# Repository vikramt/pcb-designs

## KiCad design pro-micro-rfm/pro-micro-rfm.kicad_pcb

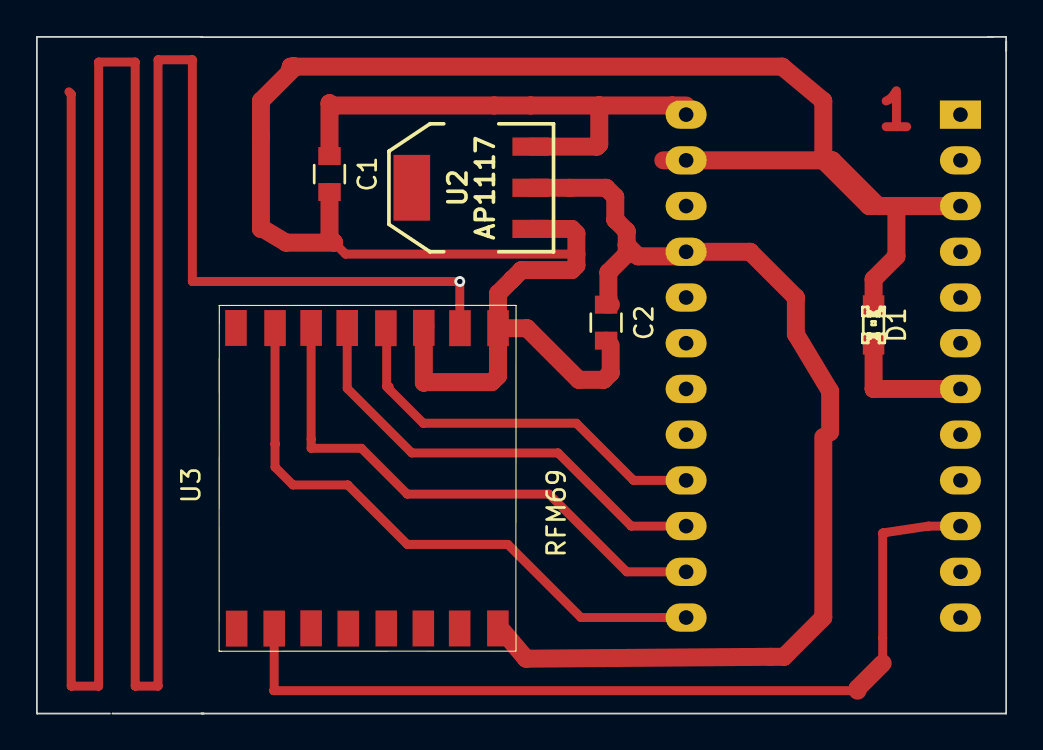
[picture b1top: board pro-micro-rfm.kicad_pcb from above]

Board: 2 copper layers, 53.8 x 37.6 mm, 6 parts (1 on the bottom side), 9 nets.

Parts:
C1, C2: C; C_0805
D1: LED; LED-0805
U1: ProMicro; ARDUINO_PRO_MINI
U2: AP1117; SOT223
U3: RFM69; RFM69HW

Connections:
GND: C1.2, C2.2, D1.1, U1.3, U1.23, U2.1, U3.9, U3.11
unnamed: C1.1, U1.24, U2.3
unnamed: C2.1, U1.21, U2.2, U3.8
unnamed: D1.2, U1.7
unnamed: U1.10, U3.2
unnamed: U1.13, U3.15
unnamed: U1.14, U3.14
unnamed: U1.15, U3.13
unnamed: U1.16, U3.12

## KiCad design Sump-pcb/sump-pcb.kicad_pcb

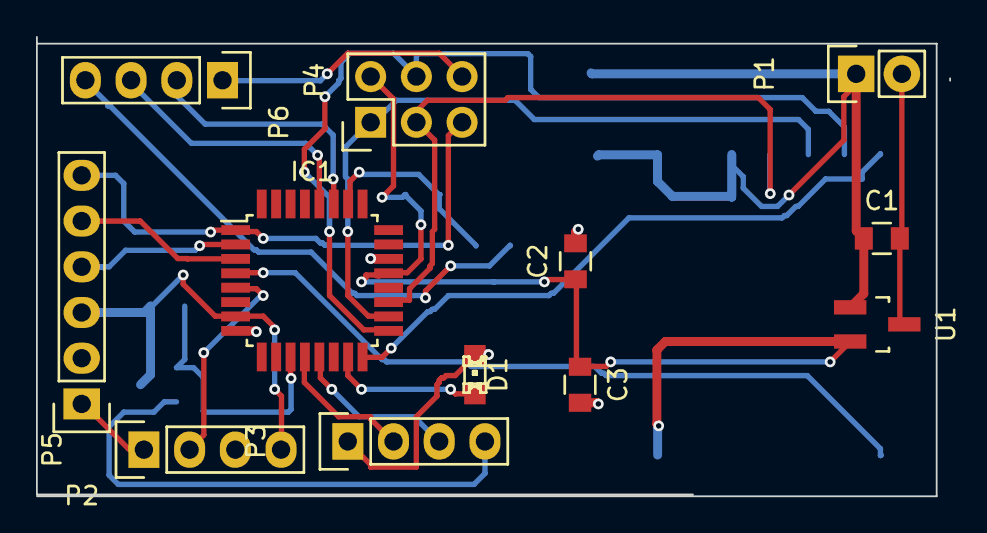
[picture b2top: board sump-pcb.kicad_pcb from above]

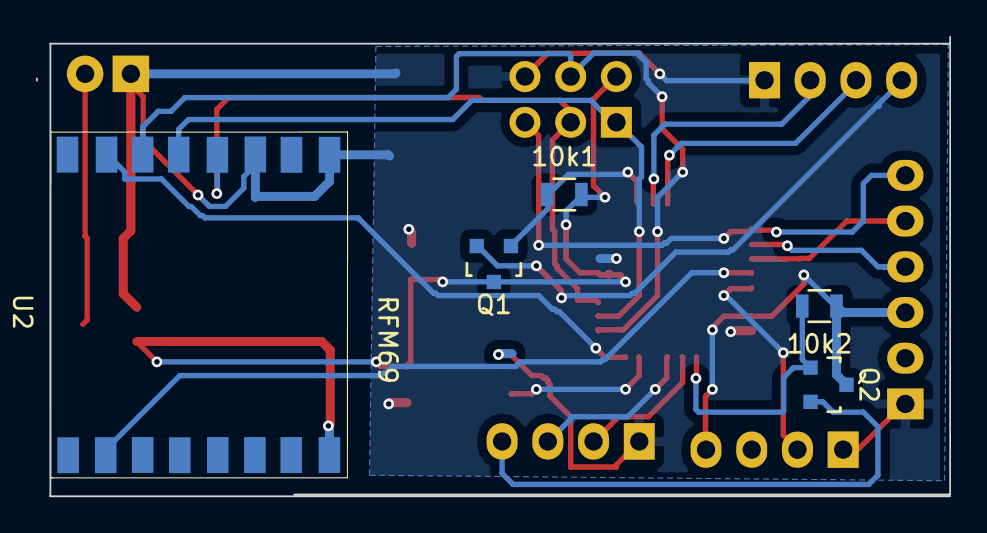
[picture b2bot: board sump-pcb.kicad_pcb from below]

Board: 2 copper layers, 50.7 x 25.5 mm, 17 parts (5 on the bottom side), 22 nets.

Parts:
10k1, 10k2: R; R_0805
C1, C2, C3: C_Small; C_0805
D1: LED; LED-0805
IC1: ATMEGA328-P; TQFP-32_7x7mm_Pitch0.8mm
P1: Vin; Pin_Header_Straight_1x02
P2: ISP; Pin_Header_Straight_1x06
P3: sonar; Pin_Header_Straight_1x04
P4: I2C; Pin_Header_Straight_1x04
P5: GPIO; Pin_Header_Straight_1x04
P6: ICSP; Pin_Header_Straight_2x03
Q1, Q2: 3401P; SOT-23
U1: AP1117D33; SOT-23_Handsoldering
U2: RFM69; RFM69HW

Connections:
+3V3: 10k1.2, 10k2.1, C2.1, C3.1, IC1.7, IC1.21, P2.3, P5.4, P6.2, Q1.3, Q2.3, U1.2, U2.8
/I2Cpower: 10k1.1, IC1.26, Q1.1
GND: C1.1, C2.2, C3.2, D1.1, IC1.8, IC1.22, P1.1, P2.1, P3.1, P4.1, P5.1, P6.6, U1.1, U2.9, U2.11
unnamed: 10k2.2, IC1.11, Q2.1
unnamed: C1.2, P1.2, U1.3
unnamed: D1.2, IC1.15
unnamed: IC1.1, P2.6, P6.5
unnamed: IC1.2, P2.4
unnamed: IC1.3, P2.5
unnamed: IC1.4, U2.2
unnamed: IC1.5, P5.2
unnamed: IC1.12, P3.2
unnamed: IC1.13, P3.3
unnamed: IC1.16, U2.15
unnamed: IC1.17, P6.4, U2.14
unnamed: IC1.18, P6.1, U2.13
unnamed: IC1.19, P6.3, U2.12
unnamed: IC1.23, P5.3
unnamed: IC1.27, P4.2
unnamed: IC1.28, P4.3
unnamed: P3.4, Q2.2
unnamed: P4.4, Q1.2

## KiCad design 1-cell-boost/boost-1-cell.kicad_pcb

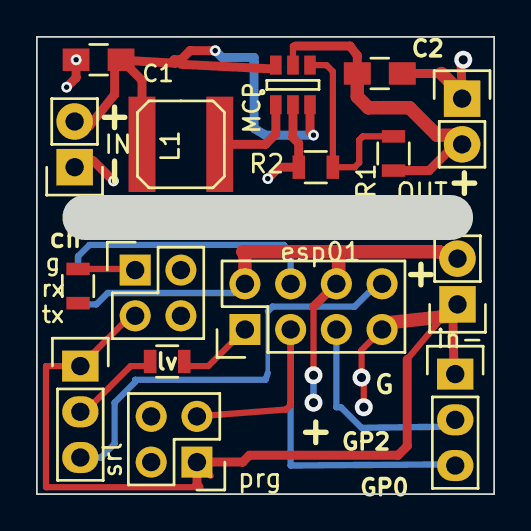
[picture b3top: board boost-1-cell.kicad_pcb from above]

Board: 2 copper layers, 25.4 x 25.4 mm, 12 parts (0 on the bottom side), 5 nets.

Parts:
C1, C2: C; C_0805_HandSoldering
L1: 10; SELF-WE-TPC_M
MCP: MCP; SOT-23-6
P1: IN; Pin_Header_Straight_1x02
P2: OUT; Pin_Header_Straight_1x02
R1, R2: R; R_0805
esp01: Pin_Header_Straight_2x04
in-: in; Pin_Header_Straight_1x02
prg: but1; Pin_Header_Straight_2x02
srl: srl; Pin_Header_Straight_1x03

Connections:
GND: C1.2, C2.2, MCP.2, P1.1, P2.1, R2.2
unnamed: C1.1, L1.1, MCP.3, MCP.6, P1.2
unnamed: C2.1, MCP.5, P2.2, R1.1
unnamed: L1.2, MCP.1
unnamed: MCP.4, R1.2, R2.1

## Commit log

2015-06-19 Initial - only 1-cell-boost - sent to oshpark
2015-06-21 added sump-pcb into git
2015-06-22 sump pcb now 2x1 with 2x mosfets
2015-06-27 got the pro-micro-rfm layed out
2015-06-28 minor pcb edits misssed sck line
